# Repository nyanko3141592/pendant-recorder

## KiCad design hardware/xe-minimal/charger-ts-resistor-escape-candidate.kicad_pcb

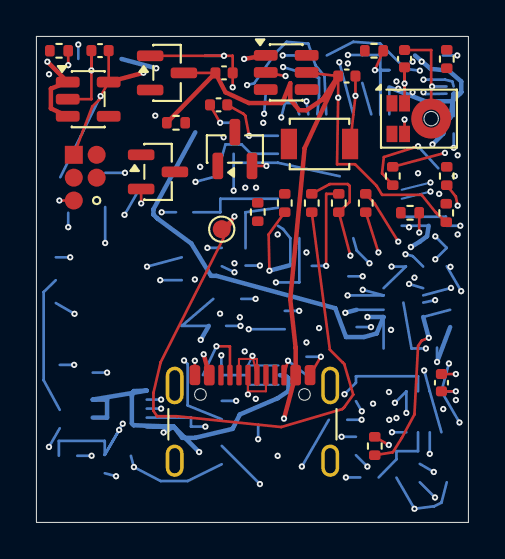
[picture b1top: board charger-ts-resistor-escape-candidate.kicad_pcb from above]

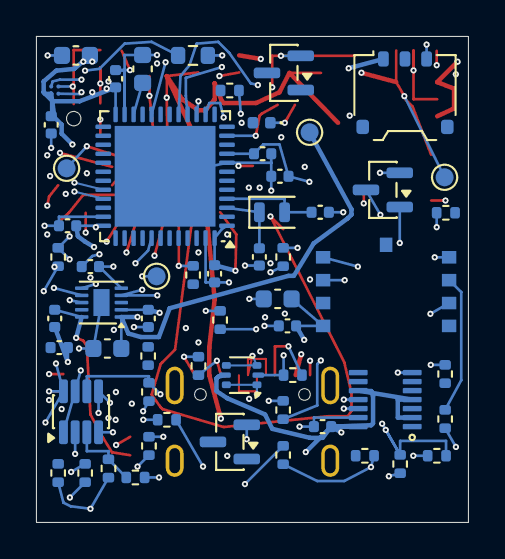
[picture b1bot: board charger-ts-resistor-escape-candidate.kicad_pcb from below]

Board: 6 copper layers, 24.0 x 27.0 mm, 89 parts (59 on the bottom side), 52 nets.

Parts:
C1, C2, C3, C6, C9, C22, C26: 100n; C_0402_1005Metric
C4: 10u; C_0603_1608Metric
C5: 4.7u; C_0603_1608Metric
C7, C16, C25: 1u; C_0402_1005Metric
C11, C12: 10p tentative; C_0402_1005Metric
C13: 2.2u 10V; C_0402_1005Metric
C14: 2.2u; C_0402_1005Metric
C15: 10u 10V effective >=1u; C_0603_1608Metric
C27: 4.7u effective TBD; C_0603_1608Metric
C28: 10n; C_0402_1005Metric
C29, C32, C33: 100n 10V; C_0402_1005Metric
C30: 50p 50V C0G; C_0402_1005Metric
C31: 1u 10V; C_0402_1005Metric
D6: amber LED 0402 TBD; LED_0402_1005Metric
J1: USB4105-GF-A (candidate); USB_C_GCT_USB4105_GroundLand112
J2: Molex781710003 / DTP401525-XE; Molex_Pico-EZmate_78171-0003_1x03-1MP_P1.20mm_Vertical
J3: Factory SWD pogo candidate; SWD_Pogo_5Pad_P1.27mm
Q3: 2N7002 (VBUS detect); SOT-23
Q4, Q5, Q6, Q7: 2N7002; SOT-23
R1: 0R; R_0402_1005Metric
R2: 10k; R_0402_1005Metric
R3, R4, R12, R13, R15, R22, R36: 100k; R_0402_1005Metric
R6, R7: 5.1k 1%; R_0402_1005Metric
R10: 6.8k 1%; R_0402_1005Metric
R11, R39: 20k 1%; R_0402_1005Metric
R14: 1M; R_0402_1005Metric
R21, R23: 22R tentative; R_0402_1005Metric
R24, R25, R28: 47k; R_0402_1005Metric
R32: 6.8k tentative; R_0402_1005Metric
R33, R34: 1M 1%; R_0402_1005Metric
R35, R43, R47, R48: 10k 1%; R_0402_1005Metric
R37, R38, R40, R45, R46, R49, R50: 100k 1%; R_0402_1005Metric
R41: 7.5k 1%; R_0402_1005Metric
R42: 130k 1%; R_0402_1005Metric
R44: 390k 1%; R_0402_1005Metric
SW1: B3U-1000P (candidate); SW_SPST_B3U-1000P
TH1: NCP18XH103F03RB 10k 1% B3380 candidate; R_0603_1608Metric
TP1, TP2, TP3, TP5, TP6: TestPoint; TestPoint_Pad_D1.0mm
U1: STM32U535CEU6; QFN-48-1EP_7x7mm_P0.5mm_EP5.6x5.6mm
U2: USBLC6-2P6; SOT-666
U3: BQ25185DLHR; Texas_DLH0010A_WSON-10-1EP_2.2x2mm_P0.4mm_EP0.9x1.5mm
U4: TPS7A0233PDBVR; SOT-23-5
U8: IM69D130V01XTSA1; IM69D130_JLC_SMD_trial
U10: TPS22916CYFPR; TPS22916_YFP4
U11: CSNP32GCR01-BOW candidate; CSNP32GCR01_LGA8
U12: TLV7042DDFR; SOT-23-8
U13: MAX4995CAUT+T; SOT-23-6
U14: SN74HCS74DYYR; Texas_DYY0014A
U15: TLV803EB29DBZR; SOT-23
Y1: 32.768kHz CL=7pF TBD; Crystal_SMD_2012-2Pin_2.0x1.2mm

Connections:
/BAT: C14.1, J2.1, R33.1, TP1.1, U3.2
/BAT_ADC: C28.1, R33.2, R34.1, U1.11
/BAT_TS: R37.2, TH1.1, U12.2, U12.5
/BOOT0: R3.1, U1.44
/BUTTON_N: R4.2, SW1.1, U1.26
/CC1: J1.A5, R6.1
/CC2: J1.B5, R7.1
/CHARGER_TS: R35.1, U3.6
/CHG_ALLOW: R43.1, U1.20
/CHG_GUARD_GATE: Q4.1, R36.1, R43.2, U12.1, U12.7
/CHG_INHIBIT_GATE: Q4.3, R12.2, U3.4
/CHG_N: R11.2, U1.27, U3.9
/GND: C1.2, C2.2, C3.2, C4.2, C5.2, C6.2, C7.2, C9.2, C11.2, C12.2, C13.2, C14.2, C15.2, C16.2, C22.2, C25.2, C26.2, C27.2, C28.2, C29.2, C30.2, C31.2, C32.2, C33.2, D6.1, J1.A1, J1.A12, J1.B1, J1.B12, J1.SH, J2.3, J3.5, Q3.2, Q4.2, Q5.2, Q6.2, Q7.2, R3.2, R6.2, R7.2, R10.2, R14.2, R22.2, R34.2, R35.2, R36.2, R39.2, R41.2, R42.2, R44.2, R46.2, R49.2, R50.2, SW1.2, TH1.2, TP6.1, U1.8, U1.23, U1.35, U1.47, U1.49, U2.2, U3.5, U3.11, U4.2, U8.4, U8.5, U10.B1, U11.4, U12.4, U13.2, U14.7, U14.11, U14.12, U14.13, U15.1
/ILIM_VSET: R42.1, U3.7
/ISET: C30.1, R10.1, U3.8
/LSE_IN: C11.1, U1.3, Y1.1
/LSE_OUT: C12.1, U1.4, Y1.2
/NRST: C9.1, J3.3, R2.2, U1.7
/PDM_CLK: R21.2, U8.3
/PDM_CLK_MCU: R21.1, U1.39
/PDM_DATA: U1.40, U8.1
/SD_CLK: R23.2, U11.3
/SD_CLK_MCU: R23.1, U1.15
/SD_CS_N: R28.2, U1.14, U11.2
/SD_EN: R22.1, U1.41, U10.B2
/SD_MISO: R25.2, U1.16, U11.6
/SD_MOSI: R24.2, U1.17, U11.5
/SD_V3: C26.1, C27.1, R24.1, R25.1, R28.1, TP5.1, U10.A1, U11.8
/STATUS_LED: R32.1, U1.29
/STATUS_LED_A: D6.2, R32.2
/SWCLK: J3.4, U1.37
/SWDIO: J3.2, U1.34
/SYS: C15.1, TP2.1, U3.1, U4.1, U4.3
/TS_COLD_REF: R38.2, R39.1, U12.3
/TS_HOT_REF: R40.2, R41.1, U12.6
/USB_DM: J1.A7, J1.B7, U1.32, U2.3, U2.4
/USB_DP: J1.A6, J1.B6, U1.33, U2.1, U2.6
/USB_HIGH_BUDGET: Q5.1, R46.1, U1.42
/USB_HIGH_BUDGET_DRAIN: Q5.3, R45.2
/USB_ILIM_SET: R44.1, R45.1, U13.3
/USB_INPUT_ON: U13.4, U14.6
/USB_LATCH_CLEAR_N: Q7.3, R48.2, U14.1, U15.2
/USB_LATCH_CLOCK: Q6.3, R47.2, U14.3
/USB_RESUME_PULSE: Q7.1, R50.1, U1.19
/USB_SUSPEND_PULSE: Q6.1, R49.1, U1.12
/V3V3: C1.1, C2.1, C3.1, C4.1, C16.1, C22.1, C25.1, C29.1, J3.1, R1.1, R2.1, R4.1, R11.1, R15.1, R37.1, R38.1, R40.1, TP3.1, U1.1, U1.24, U1.36, U1.48, U4.5, U8.2, U10.A2, U12.8
/VBUS: C31.1, C32.1, C33.1, J1.A4, J1.A9, J1.B4, J1.B9, R13.1, R47.1, R48.1, U2.5, U13.5, U14.2, U14.4, U14.10, U14.14, U15.3
/VBUS_GATE: Q3.1, R13.2, R14.1
/VBUS_LIMITED: C13.1, R12.1, U3.10, U13.1
/VBUS_N: Q3.3, R15.2, U1.10
/VCAP: C5.1, U1.22
/VDDA: C6.1, C7.1, R1.2, U1.9

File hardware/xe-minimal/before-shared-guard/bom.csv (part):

Reference,Part/value,Footprint,Design note
U1,STM32U535CEU6,Package_DFN_QFN:QFN-48-1EP_7x7mm_P0.5mm_EP5.6x5.6mm,512KB Flash/274KB RAM; non-SMPS UFQFPN48. PB3/PB4 ADF AF3; PA5/6/7 SPI1 AF5. VDD USB shared 3.3V. JLC acceptance and pin review pending.
C1,100n,Capacitor_SMD:C_0402_1005Metric,
C4,10u,Capacitor_SMD:C_0603_1608Metric,Main bulk capacitor; check startup and effective capacitance.
C9,100n,Capacitor_SMD:C_0402_1005Metric,
R2,10k,Resistor_SMD:R_0402_1005Metric,
Y1,32.768kHz CL=7pF TBD,Crystal:Crystal_SMD_2012-2Pin_2.0x1.2mm,
C11,10p tentative,Capacitor_SMD:C_0402_1005Metric,
C12,10p tentative,Capacitor_SMD:C_0402_1005Metric,
J3,Factory SWD pogo candidate,PendantMinimal:SWD_Pogo_5Pad_P1.27mm,Five exposed pads; factory fixture required; VTref sense only. No buyer flashing.
SW1,B3U-1000P (candidate),Button_Switch_SMD:SW_SPST_B3U-1000P,
R4,100k,Resistor_SMD:R_0402_1005Metric,
J1,USB4105-GF-A (candidate),PendantD1:USB_C_GCT_USB4105_GroundLand112,Exact footprint and shield pad numbering pending connector selection
R6,5.1k 1%,Resistor_SMD:R_0402_1005Metric,
R7,5.1k 1%,Resistor_SMD:R_0402_1005Metric,
U2,USBLC6-2P6,Package_TO_SOT_SMD:SOT-666,"ST DS4260 same 6-pin function diagram; smaller package, LCSC C15999 catalog; orientation/land pattern final audit pending."
C13,2.2u 10V,Capacitor_SMD:C_0402_1005Metric,
U3,BQ25185DLHR,Package_DFN_QFN:Texas_DLH0010A_WSON-10-1EP_2.2x2mm_P0.4mm_EP0.9x1.5mm,XE candidate4.1V ±0.5% =>4.1205V upper;44.12mA nominal charging. ILIM500 requires host power policy; thermal contact and battery capacity at4.1V unqualified; charge inhibited.
R10,6.8k 1%,Resistor_SMD:R_0402_1005Metric,XE prototype44.12mA nominal;10%IC/1%R screen39.31..49.02mA below110mA pack maximum. Nominal4.41mA termination exceeds manufacturer1.1mA reference; capacity/16h not guaranteed. No charge enable.
R11,20k 1%,Resistor_SMD:R_0402_1005Metric,
C14,2.2u,Capacitor_SMD:C_0402_1005Metric,
J2,Molex781710003 / DTP401525-XE,Connector_Molex:Molex_Pico-EZmate_78171-0003_1x03-1MP_P1.20mm_Vertical,"Pack manufacturer p9:1red+,2NTC,3black-. Header mating-view pad alignment still requires validation. Built-in NTC has no identified R-T curve; pin2 deliberately NC. Independent factory-mountedTH1 contact sensor is mandatory; no user soldering. Reverse polarity protection review pending."
R12,100k,Resistor_SMD:R_0402_1005Metric,100k VBUS pull-up defaults Q2 to charge inhibited; no MCU GPIO connection to5V.
C15,10u 10V effective >=1u,Capacitor_SMD:C_0603_1608Metric,SYS cap per TI; DC-bias capacitance must be qualified.
U4,TPS7A0233PDBVR,Package_TO_SOT_SMD:SOT-23-5,3.3V main rail: 48-pin MCU has no separate USB supply; dropout/capacity measurement required.
C16,1u,Capacitor_SMD:C_0402_1005Metric,
U8,IM69D130V01XTSA1,Pendant:IM69D130_JLC_SMD_trial,"Direct 3.3V PDM, bottom port; no AAD. 0.768MHz/decimation48 candidate for 16kHz; acoustic validation required."
R21,22R tentative,Resistor_SMD:R_0402_1005Metric,
C22,100n,Capacitor_SMD:C_0402_1005Metric,
U10,TPS22916CYFPR,Pendant:TPS22916_YFP4,Omi SD switch; power-off sequence must tristate ALL SD signals
R22,100k,Resistor_SMD:R_0402_1005Metric,
C25,1u,Capacitor_SMD:C_0402_1005Metric,
R23,22R tentative,Resistor_SMD:R_0402_1005Metric,
R24,47k,Resistor_SMD:R_0402_1005Metric,
R25,47k,Resistor_SMD:R_0402_1005Metric,
R28,47k,Resistor_SMD:R_0402_1005Metric,
C26,100n,Capacitor_SMD:C_0402_1005Metric,
C27,4.7u effective TBD,Capacitor_SMD:C_0603_1608Metric,
TP1,TestPoint,TestPoint:TestPoint_Pad_D1.0mm,
TP2,TestPoint,TestPoint:TestPoint_Pad_D1.0mm,
TP3,TestPoint,TestPoint:TestPoint_Pad_D1.0mm,
TP5,TestPoint,TestPoint:TestPoint_Pad_D1.0mm,
TP6,TestPoint,TestPoint:TestPoint_Pad_D1.0mm,
R32,6.8k tentative,Resistor_SMD:R_0402_1005Metric,"LED current target 0.1-0.2mA; verify LED Vf, daylight readability and GPIO limits"
D6,amber LED 0402 TBD,LED_SMD:LED_0402_1005Metric,"Single status/battery indicator; firmware blinks on demand, normally dark."
C2,100n,Capacitor_SMD:C_0402_1005Metric,
C3,100n,Capacitor_SMD:C_0402_1005Metric,
C5,4.7u,Capacitor_SMD:C_0603_1608Metric,
C6,100n,Capacitor_SMD:C_0402_1005Metric,
C7,1u,Capacitor_SMD:C_0402_1005Metric,
R1,0R,Resistor_SMD:R_0402_1005Metric,
R3,100k,Resistor_SMD:R_0402_1005Metric,
Q3,2N7002 (VBUS detect),Package_TO_SOT_SMD:SOT-23,
R13,100k,Resistor_SMD:R_0402_1005Metric,
R14,1M,Resistor_SMD:R_0402_1005Metric,
R15,100k,Resistor_SMD:R_0402_1005Metric,
R33,1M 1%,Resistor_SMD:R_0402_1005Metric,"Battery divider 1:2; sample after settling, calibrate with VREFINT; not coulomb counting."
R34,1M 1%,Resistor_SMD:R_0402_1005Metric,"Battery divider 1:2; sample after settling, calibrate with VREFINT; not coulomb counting."
C28,10n,Capacitor_SMD:C_0402_1005Metric,"Battery divider 1:2; sample after settling, calibrate with VREFINT; not coulomb counting."
R35,10k 1%,Resistor_SMD:R_0402_1005Metric,Holds normal TS level when released; no floating TS/TTDM in intended circuit.
R36,100k,Resistor_SMD:R_0402_1005Metric,MCU reset/high-Z defaults to no charging permission.
R37,100k 1%,Resistor_SMD:R_0402_1005Metric,Reduce thermistor excitation; 5.25V and99k gives52.99uA maximum branch current and69.60uW maximum thermistor power. Only powered from USB.
R38,100k 1%,Resistor_SMD:R_0402_1005Metric,
R39,20k 1%,Resistor_SMD:R_0402_1005Metric,Cold threshold candidate. Beta-model sensitivity is not full manufacturer R-T qualification. See temperature-screen.json.
R40,100k 1%,Resistor_SMD:R_0402_1005Metric,
R41,7.5k 1%,Resistor_SMD:R_0402_1005Metric,Hot threshold candidate. Reserve margin for contact sensor lag; physical thermal qualification required.
U12,TLV7042DDFR,Package_TO_SOT_SMD:SOT-23-8,"Open-drain wired-AND temperature permission. Either fault pulls Q4 gate low. Board NTC replaces undocumented pack NTC; exact R-T, common-mode error and thermal contact not qualified."
Q4,2N7002,Package_TO_SOT_SMD:SOT-23,"Pulls BQ25185 CE_N low only when MCU and wired-AND comparator outputs permit. R36 defaults gate low. Startup, leakage and gate-voltage behavior need review."
C29,100n 10V,Capacitor_SMD:C_0402_1005Metric,Place adjacent to U12 supply pins.
R42,130k 1%,Resistor_SMD:R_0402_1005Metric,BQ25185 Table6-1:4.1V / ILIM500. Input450/475/498mA. Requires USB preconfiguration/suspend power management; charge stays disabled pending qualification.
C30,50p 50V C0G,Capacitor_SMD:C_0402_1005Metric,BQ25185 SLUSF65B6.1.1.4 low-current <50mA recommendation; final transient behavior requires hardware test.
R43,10k 1%,Resistor_SMD:R_0402_1005Metric,MCU permission series resistor; limits current into comparator fault clamp.
TH1,NCP18XH103F03RB 10k 1% B3380 candidate,Resistor_SMD:R_0603_1608Metric,Independent factory-mounted contactNTC required because pack NTC exactR-T unspecified. Electrically insulated compliant contact to pouch and retention must be engineered and tested; no ambient-only charging approval.
U13,MAX4995CAUT+T,Package_TO_SOT_SMD:SOT-23-6,Continuous input limiter; DC screen3.3V only; FLAG explicitlyNC. Not charging qualification.
U14,SN74HCS74DYYR,Pendant_Input:Texas_DYY0014A,RawVBUS retainedOFF latch; Schmitt inputs. POR/resume clearQ=0 =>Q_N enables input. Suspend clocksD=1 =>Q_N disables. UnusedFF heldclear; PRE alwayshigh.
U15,TLV803EB29DBZR,Package_TO_SOT_SMD:SOT-23,"2.93V supervisor;B40us nominal/80us maxunderdatasheetcondition. StandardDBZ pinout, NOT RDBZ or VDBZ. Initializes latch before chargerUVLO; analog startup still needs validation."
R44,390k 1%,Resistor_SMD:R_0402_1005Metric,Input control candidate; tolerance/assembly/physical layout pending
R45,100k 1%,Resistor_SMD:R_0402_1005Metric,Input control candidate; tolerance/assembly/physical layout pending
Q5,2N7002,Package_TO_SOT_SMD:SOT-23,Ground-referenced gate; verify exact vendor leakage/capacitance and low-current sink at3.3V
R46,100k 1%,Resistor_SMD:R_0402_1005Metric,Input control candidate; tolerance/assembly/physical layout pending
R47,10k 1%,Resistor_SMD:R_0402_1005Metric,Input control candidate; tolerance/assembly/physical layout pending
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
